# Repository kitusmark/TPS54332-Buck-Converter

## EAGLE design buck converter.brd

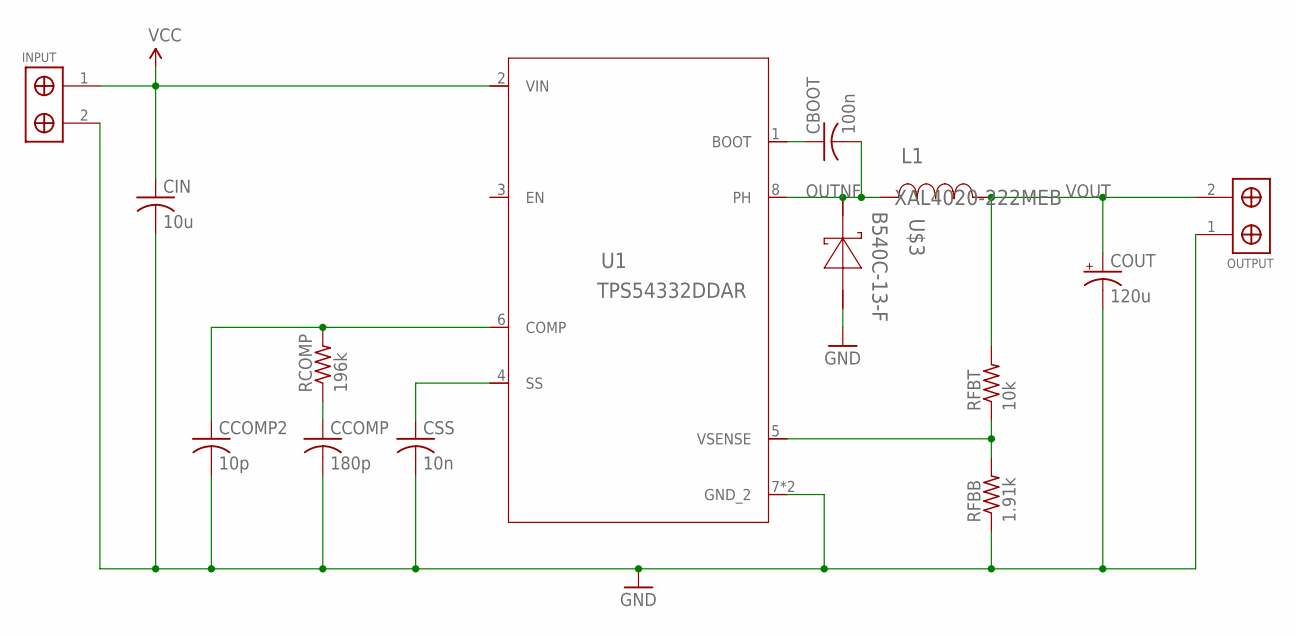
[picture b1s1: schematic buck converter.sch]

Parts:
CBOOT: 100n; C0805
CCOMP: 180p; C0805
CCOMP2: 10p; C0805
CIN: 10u; C1210
COUT: 120u; D/7343-31R
CSS: 10n; C0805
INPUT: SCREW_TERMINALS; 1X02-5MM
L1: XAL4020-222MEB; XAL4020
OUTPUT: SCREW_TERMINALS; 1X02-5MM
RCOMP: 196k; R0805
RFBB: 1.91k; R0805
RFBT: 10k; R0805
U1: TPS54332DDAR; DDA0008H
U$3: B540C-13-F; SMC

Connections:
GND: CCOMP.2, CCOMP2.2, CIN.2, COUT.-, CSS.2, INPUT.2, OUTPUT.1, RFBB.1, U1.7 (GND_2), U1.9 (GND_2), U$3.2 (A)
unnamed: CCOMP.1, RCOMP.1
unnamed: CCOMP2.1, RCOMP.2, U1.6 (COMP)
unnamed: CSS.1, U1.4 (SS)
unnamed: RFBB.2, RFBT.1, U1.5 (VSENSE)
unnamed: CBOOT.1, U1.1 (BOOT)
OUTNF: CBOOT.2, L1.1, U1.8 (PH), U$3.1 (K)
VCC: CIN.1, INPUT.1, U1.2 (VIN)
VOUT: COUT.+, L1.2, OUTPUT.2, RFBT.2

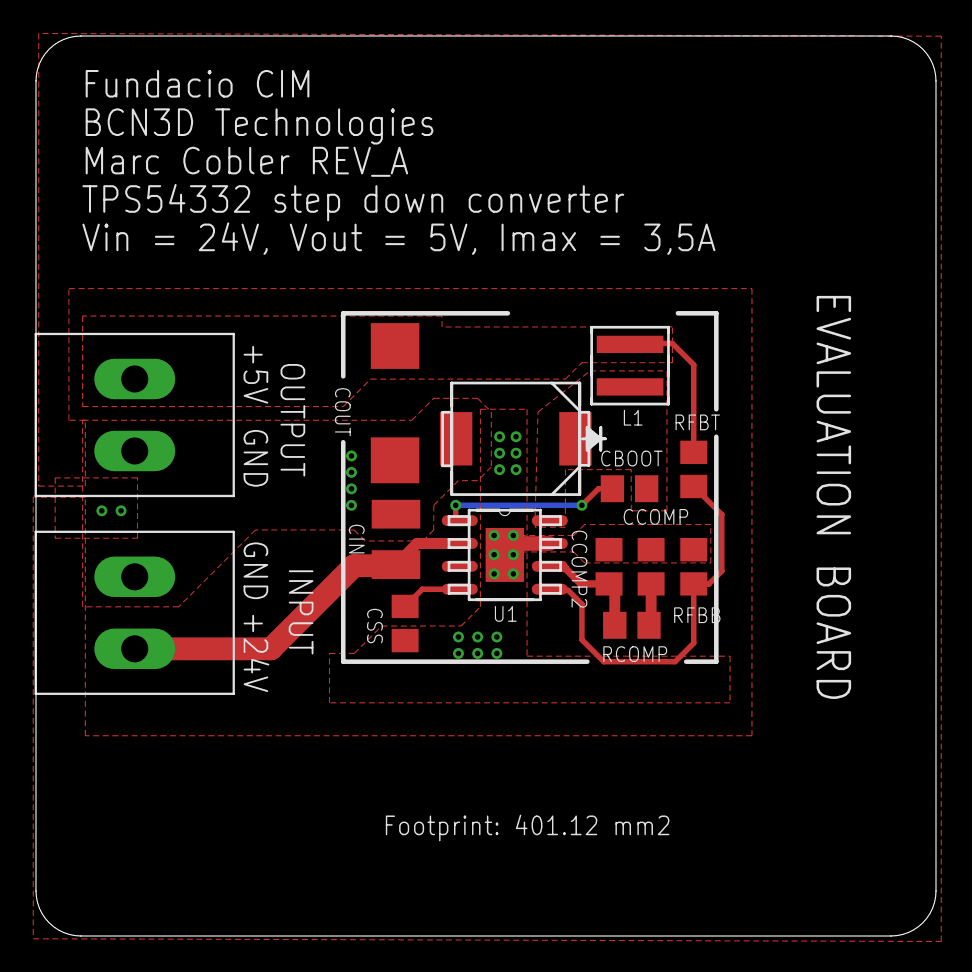
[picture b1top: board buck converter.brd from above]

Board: 2 copper layers, 50.0 x 50.0 mm, 15 parts (1 on the bottom side), 9 nets.

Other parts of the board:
U$1: BCN3D_LOGO

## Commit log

2016-06-16 All files of working version
2016-06-16 Update gitignore for eagle

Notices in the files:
parts and their libraries:
SparkFun-Aesthetics: Licensing: Creative Commons ShareAlike 4.0 International - https://creativecommons.org/licenses/by-sa/4.0
